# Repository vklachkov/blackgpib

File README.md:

# BlackGPIB

BlackGPIB is hardware that emulates GPIB disk drives for the GRiD Compass. It is based on the Raspberry Pi RP2040.

## Hardware

Hardware schematics and design files are located in the `hardware` folder. Production files are available in the [latest release](github.com/vklachkov/blackgpib/releases) on GitHub.

We recommend using the latest `pico` version. The list of components and known issues is described in the `README.md` file located in the `hardware/pico` directory.

## Firmware

The firmware source code is located in the `pico` folder.

The latest stable prebuilt firmware in UF2 format is available in the [latest release](https://github.com/vklachkov/blackgpib/releases) on GitHub.

### Flashing prebuilt firmware

To flash the firmware, hold the **BOOTSEL** button while connecting the Raspberry Pi Pico to your computer. The Pico will appear as a removable drive.

Copy the `blackgpib.uf2` file to this drive. The Pico will reboot automatically after the file is copied.

### Building firmware from source

To build the firmware yourself, install the Pico SDK first. Follow the instructions on the official Raspberry Pi website:

https://www.raspberrypi.com/documentation/microcontrollers/c_sdk.html

Then follow these steps.

1. Clone the repository:

```bash
git clone --depth 1 --recursive https://github.com/vklachkov/blackgpib
```

2. Go to the sources directory:

```bash
cd blackgpib/pico
```

3. Configure the project for your board:

```bash
cmake -S . -B build -DPICO_BOARD=pico
```

4. Build:

```bash
cmake --build build -j
```

5. Flash the firmware:

   Hold the **BOOTSEL** button while connecting the Raspberry Pi Pico to your computer. Then copy the `blackgpib.uf2` file from the `build` folder to the mounted Pico drive.

## How to use it?

After assembling and flashing the device, find a microSD card and format it as FAT32 or exFAT. Copy the disk images to this card. Insert the microSD card into BlackGPIB. Connect BlackGPIB to power, the LED should turn on after about one and a half seconds. After that, you can turn on the GRiD Compass. Enjoy!

### Which file formats are supported?

Currently, only .IMG files are supported. IMD and .CHD are not supported.

If you want to use IMD files from gridrepository.org, please use the [imd2raw](https://github.com/RetroFloppy/imd2raw) converter until BlackGPIB support is not available.

### How is the address selected?

For images that do not have a GPIB address specified in their filename, the address is selected automatically.

Floppy disk images use addresses 5, 6, and 13. Other images use the remaining default addresses (4, 5, 6, 12, 13).

If addresses conflict, or if there are no addresses left, an entry about this will be written to log.txt.

### How do I bind an image to a specific GPIB address?

Rename the image to FXX or HXX, where XX is the GPIB address. For example, FLOPPY4_TEST.IMG or HD12.IMG.

### How do I change the image geometry?

You can’t, it is selected automatically. Geometry configuration is not supported.

### Troubleshooting

**The LED is always off**

Check that you assembled the emulator correctly, powered it, and flashed the correct firmware.

**The device is steadily blinking the LED on the board**

This means that the device does not see the SD card, or the filesystem on it is not FAT.

Remove the SD card, format it again, and insert it into the device. If you did not disconnect power from BlackGPIB, then, if successful, the device will blink the LED several times, and then the LED should stay steadily on. This means that the device is ready to use.

**The device is blinking SOS**

This means that the device has gone into a boot loop. Normally, this should not happen.

Connect the device to your computer, open a serial port monitor, and check what went wrong before the boot loop. You can email me or open an issue, and I will try to help.

## License

This project is released under the [MIT License](LICENSE).

You are free to use, modify, and share it. I will be happy if BlackGPIB helps you bring your GRiD Compass back to life and use it again.

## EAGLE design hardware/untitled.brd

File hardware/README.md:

# First board by @JDat for Raspberry Pi 2+

This is the first revision of the board, designed by @JDat (also known as @YL3AKC):

> [!WARNING]
> It is better to wait for the second revision or new Pico base version. This board is still experimental.

## Components

| Part           | Value                | Package    | Quantity |
|----------------|----------------------|------------|----------|
| GPIB Connector | -                    | 90 Degree  | 1        |
| SN75160B       | -                    | SMD or DIP | 1        |
| SN75161B       | -                    | SMD or DIP | 1        |
| Resistor       | 2kΩ                  | 0805       | 20       |
| Capacitor      | 0.1uF                | 0805       | 2        |
| Pin Header     | 20x2 Straight Female | -          | 1        |

P.S. Instead of small SMD components, you can also use through-hole components, as Kirill @BOOtak Leyfer did.

https://t.me/bootaks_old_devices/286

## Errata

### ATN <-> SRQ

ATN and SRQ are mixed up on the board. Both the labels and the pins on the connector are swapped.

For the board to work correctly, you need to cut two tracks on the back side that go to SRQ and ATN, and solder two jumpers, as shown in the photo:

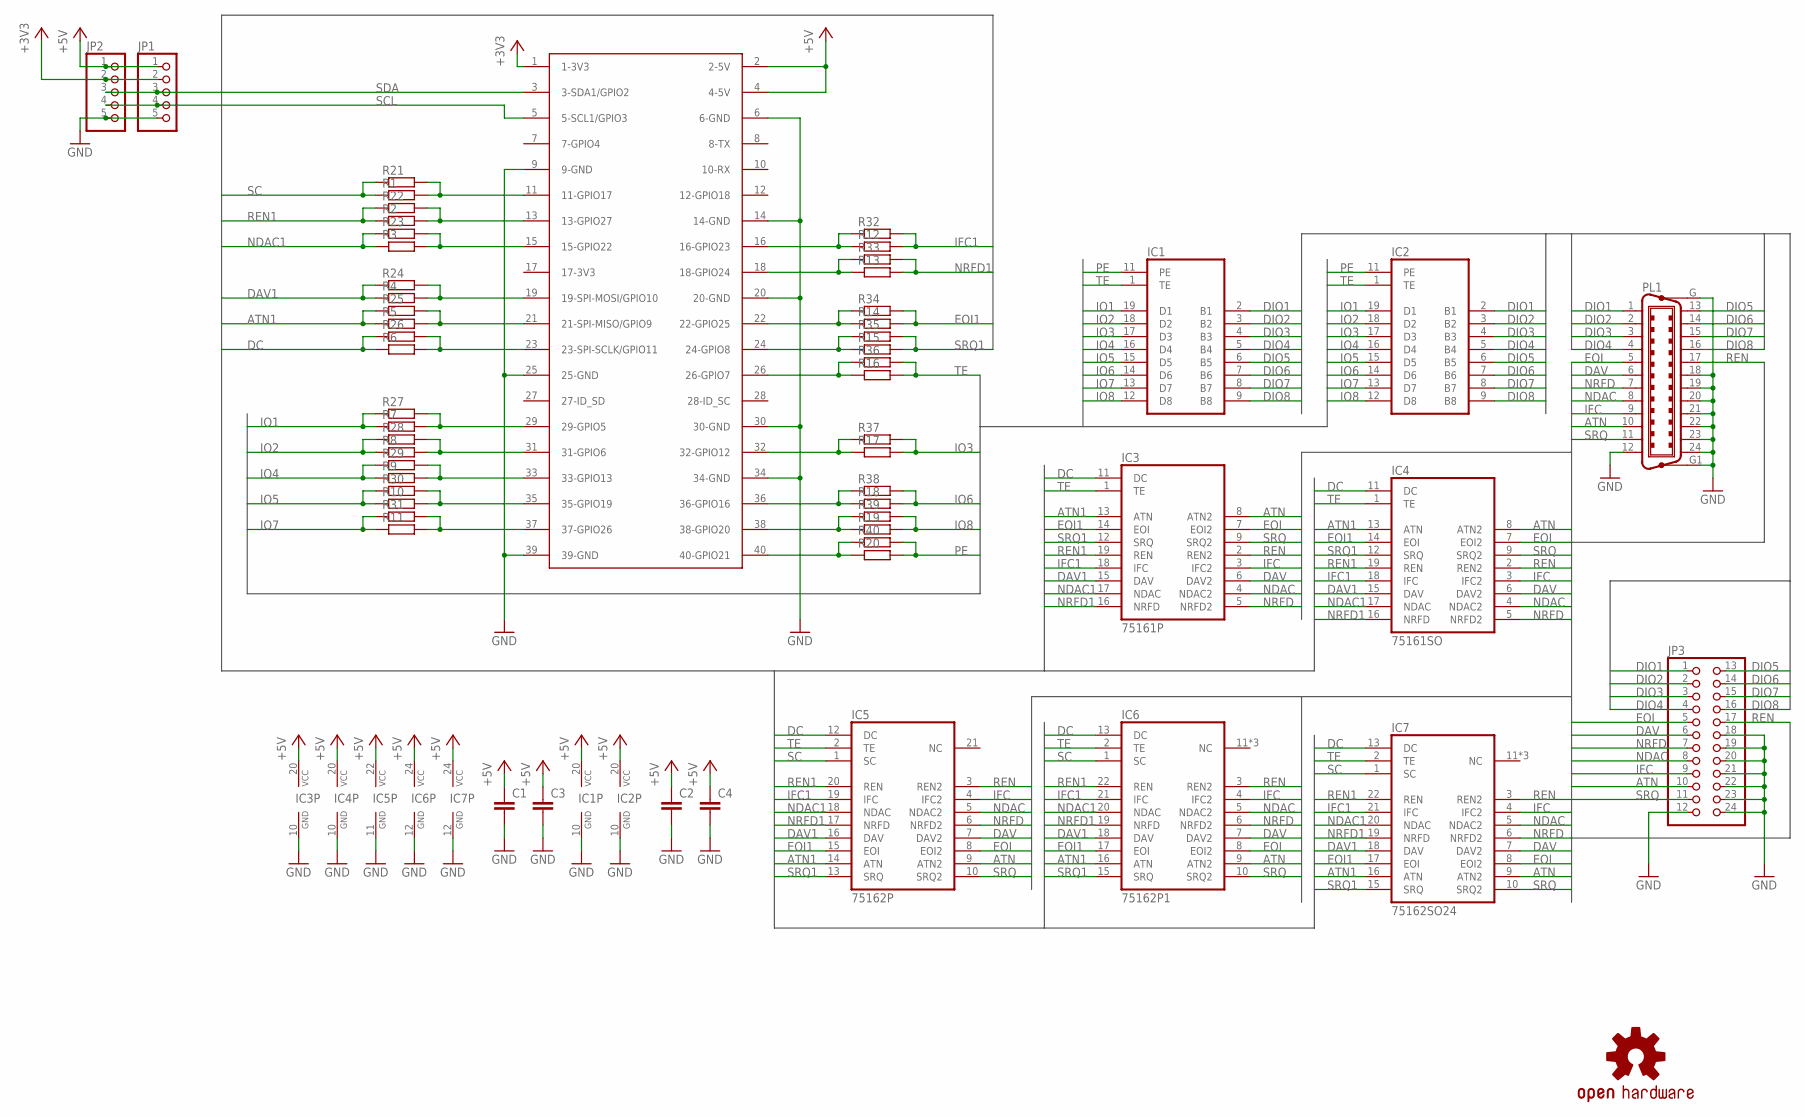
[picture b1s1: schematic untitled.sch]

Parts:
C1, C2: C-EUC0805; C0805
C3, C4: C-EU050-024X044; C050-024X044
IC1: 75160P; DIL20
IC2: 75160SO; SO20L
IC3: 75161P; DIL20
IC4: 75161SO; SO20L
IC5: 75162P; DIL22-3
IC6: 75162P1; DIL24-3
IC7: 75162SO24; SOIC127P1030X265-24N
JP1, JP2: PINHD-1X5; 1X05
JP3: GPIB-PINHD-2X12
LOGO2: OSHW-LOGOS; OSHW-LOGO-S
PL1: C24HP; 24HP
R1, R2, R3, R4, R5, R6, R7, R8, R9, R10, R11, R12, R13, R14, R15, R16, R17, R18, R19, R20: R-EU_R0805; R0805
R21, R22, R23, R24, R25, R26, R27, R28, R29, R30, R31, R32, R33, R34, R35, R36, R37, R38, R39, R40: R-EU_0204/7; 0204/7
U$2: RASPBERRY-PI+HEADERONLY; RASPBERRY-PI-PLUS-HEADERONLY

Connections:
+3V3: JP1.2, JP2.2, U$2.1 (1-3V3)
+5V: C1.1, C2.1, C3.1, C4.1, IC1.20 (VCC), IC2.20 (VCC), IC3.20 (VCC), IC4.20 (VCC), IC5.22 (VCC), IC6.24 (VCC), IC7.24 (VCC), JP1.1, JP2.1, U$2.2 (2-5V), U$2.4 (4-5V)
ATN: IC3.8 (ATN2), IC4.8 (ATN2), IC5.9 (ATN2), IC6.9 (ATN2), IC7.9 (ATN2), JP3.10, PL1.10
ATN1: IC3.13 (ATN), IC4.13 (ATN), IC5.14 (ATN), IC6.16 (ATN), IC7.16 (ATN), R5.1, R25.1
DAV: IC3.6 (DAV2), IC4.6 (DAV2), IC5.7 (DAV2), IC6.7 (DAV2), IC7.7 (DAV2), JP3.6, PL1.6
DAV1: IC3.15 (DAV), IC4.15 (DAV), IC5.16 (DAV), IC6.18 (DAV), IC7.18 (DAV), R4.1, R24.1
DC: IC3.11 (DC), IC4.11 (DC), IC5.12 (DC), IC6.13 (DC), IC7.13 (DC), R6.1, R26.1
DIO1: IC1.2 (B1), IC2.2 (B1), JP3.1, PL1.1
DIO2: IC1.3 (B2), IC2.3 (B2), JP3.2, PL1.2
DIO3: IC1.4 (B3), IC2.4 (B3), JP3.3, PL1.3
DIO4: IC1.5 (B4), IC2.5 (B4), JP3.4, PL1.4
DIO5: IC1.6 (B5), IC2.6 (B5), JP3.13, PL1.13
DIO6: IC1.7 (B6), IC2.7 (B6), JP3.14, PL1.14
DIO7: IC1.8 (B7), IC2.8 (B7), JP3.15, PL1.15
DIO8: IC1.9 (B8), IC2.9 (B8), JP3.16, PL1.16
EOI: IC3.7 (EOI2), IC4.7 (EOI2), IC5.8 (EOI2), IC6.8 (EOI2), IC7.8 (EOI2), JP3.5, PL1.5
EOI1: IC3.14 (EOI), IC4.14 (EOI), IC5.15 (EOI), IC6.17 (EOI), IC7.17 (EOI), R14.2, R34.2
GND: C1.2, C2.2, C3.2, C4.2, IC1.10 (GND), IC2.10 (GND), IC3.10 (GND), IC4.10 (GND), IC5.11 (GND), IC6.12 (GND), IC7.12 (GND), JP1.5, JP2.5, JP3.12, JP3.18, JP3.19, JP3.20, JP3.21, JP3.22, JP3.23, JP3.24, PL1.12, PL1.18, PL1.19, PL1.20, PL1.21, PL1.22, PL1.23, PL1.24, PL1.G, PL1.G1, U$2.6 (6-GND), U$2.9 (9-GND), U$2.14 (14-GND), U$2.20 (20-GND), U$2.25 (25-GND), U$2.30 (30-GND), U$2.34 (34-GND), U$2.39 (39-GND)
IFC: IC3.3 (IFC2), IC4.3 (IFC2), IC5.4 (IFC2), IC6.4 (IFC2), IC7.4 (IFC2), JP3.9, PL1.9
IFC1: IC3.18 (IFC), IC4.18 (IFC), IC5.19 (IFC), IC6.21 (IFC), IC7.21 (IFC), R12.2, R32.2
IO1: IC1.19 (D1), IC2.19 (D1), R7.1, R27.1
IO2: IC1.18 (D2), IC2.18 (D2), R8.1, R28.1
IO3: IC1.17 (D3), IC2.17 (D3), R17.2, R37.2
IO4: IC1.16 (D4), IC2.16 (D4), R9.1, R29.1
IO5: IC1.15 (D5), IC2.15 (D5), R10.1, R30.1
IO6: IC1.14 (D6), IC2.14 (D6), R18.2, R38.2
IO7: IC1.13 (D7), IC2.13 (D7), R11.1, R31.1
IO8: IC1.12 (D8), IC2.12 (D8), R19.2, R39.2
unnamed: R1.2, R21.2, U$2.11 (11-GPIO17)
unnamed: R2.2, R22.2, U$2.13 (13-GPIO27)
unnamed: R3.2, R23.2, U$2.15 (15-GPIO22)
unnamed: R4.2, R24.2, U$2.19 (19-SPI-MOSI/GPIO10)
unnamed: R5.2, R25.2, U$2.21 (21-SPI-MISO/GPIO9)
unnamed: R6.2, R26.2, U$2.23 (23-SPI-SCLK/GPIO11)
unnamed: R7.2, R27.2, U$2.29 (29-GPIO5)
unnamed: R8.2, R28.2, U$2.31 (31-GPIO6)
unnamed: R9.2, R29.2, U$2.33 (33-GPIO13)
unnamed: R10.2, R30.2, U$2.35 (35-GPIO19)
unnamed: R11.2, R31.2, U$2.37 (37-GPIO26)
unnamed: R12.1, R32.1, U$2.16 (16-GPIO23)
unnamed: R13.1, R33.1, U$2.18 (18-GPIO24)
unnamed: R14.1, R34.1, U$2.22 (22-GPIO25)
unnamed: R15.1, R35.1, U$2.24 (24-GPIO8)
unnamed: R16.1, R36.1, U$2.26 (26-GPIO7)
unnamed: R17.1, R37.1, U$2.32 (32-GPIO12)
unnamed: R18.1, R38.1, U$2.36 (36-GPIO16)
unnamed: R19.1, R39.1, U$2.38 (38-GPIO20)
unnamed: R20.1, R40.1, U$2.40 (40-GPIO21)
NDAC: IC3.4 (NDAC2), IC4.4 (NDAC2), IC5.5 (NDAC2), IC6.5 (NDAC2), IC7.5 (NDAC2), JP3.8, PL1.8
NDAC1: IC3.17 (NDAC), IC4.17 (NDAC), IC5.18 (NDAC), IC6.20 (NDAC), IC7.20 (NDAC), R3.1, R23.1
NRFD: IC3.5 (NRFD2), IC4.5 (NRFD2), IC5.6 (NRFD2), IC6.6 (NRFD2), IC7.6 (NRFD2), JP3.7, PL1.7
NRFD1: IC3.16 (NRFD), IC4.16 (NRFD), IC5.17 (NRFD), IC6.19 (NRFD), IC7.19 (NRFD), R13.2, R33.2
PE: IC1.11 (PE), IC2.11 (PE), R20.2, R40.2
REN: IC3.2 (REN2), IC4.2 (REN2), IC5.3 (REN2), IC6.3 (REN2), IC7.3 (REN2), JP3.17, PL1.17
REN1: IC3.19 (REN), IC4.19 (REN), IC5.20 (REN), IC6.22 (REN), IC7.22 (REN), R2.1, R22.1
SC: IC5.1 (SC), IC6.1 (SC), IC7.1 (SC), R1.1, R21.1
SCL: JP1.4, JP2.4, U$2.5 (5-SCL1/GPIO3)
SDA: JP1.3, JP2.3, U$2.3 (3-SDA1/GPIO2)
SRQ: IC3.9 (SRQ2), IC4.9 (SRQ2), IC5.10 (SRQ2), IC6.10 (SRQ2), IC7.10 (SRQ2), JP3.11, PL1.11
SRQ1: IC3.12 (SRQ), IC4.12 (SRQ), IC5.13 (SRQ), IC6.15 (SRQ), IC7.15 (SRQ), R15.2, R35.2
TE: IC1.1 (TE), IC2.1 (TE), IC3.1 (TE), IC4.1 (TE), IC5.2 (TE), IC6.2 (TE), IC7.2 (TE), R16.2, R36.2

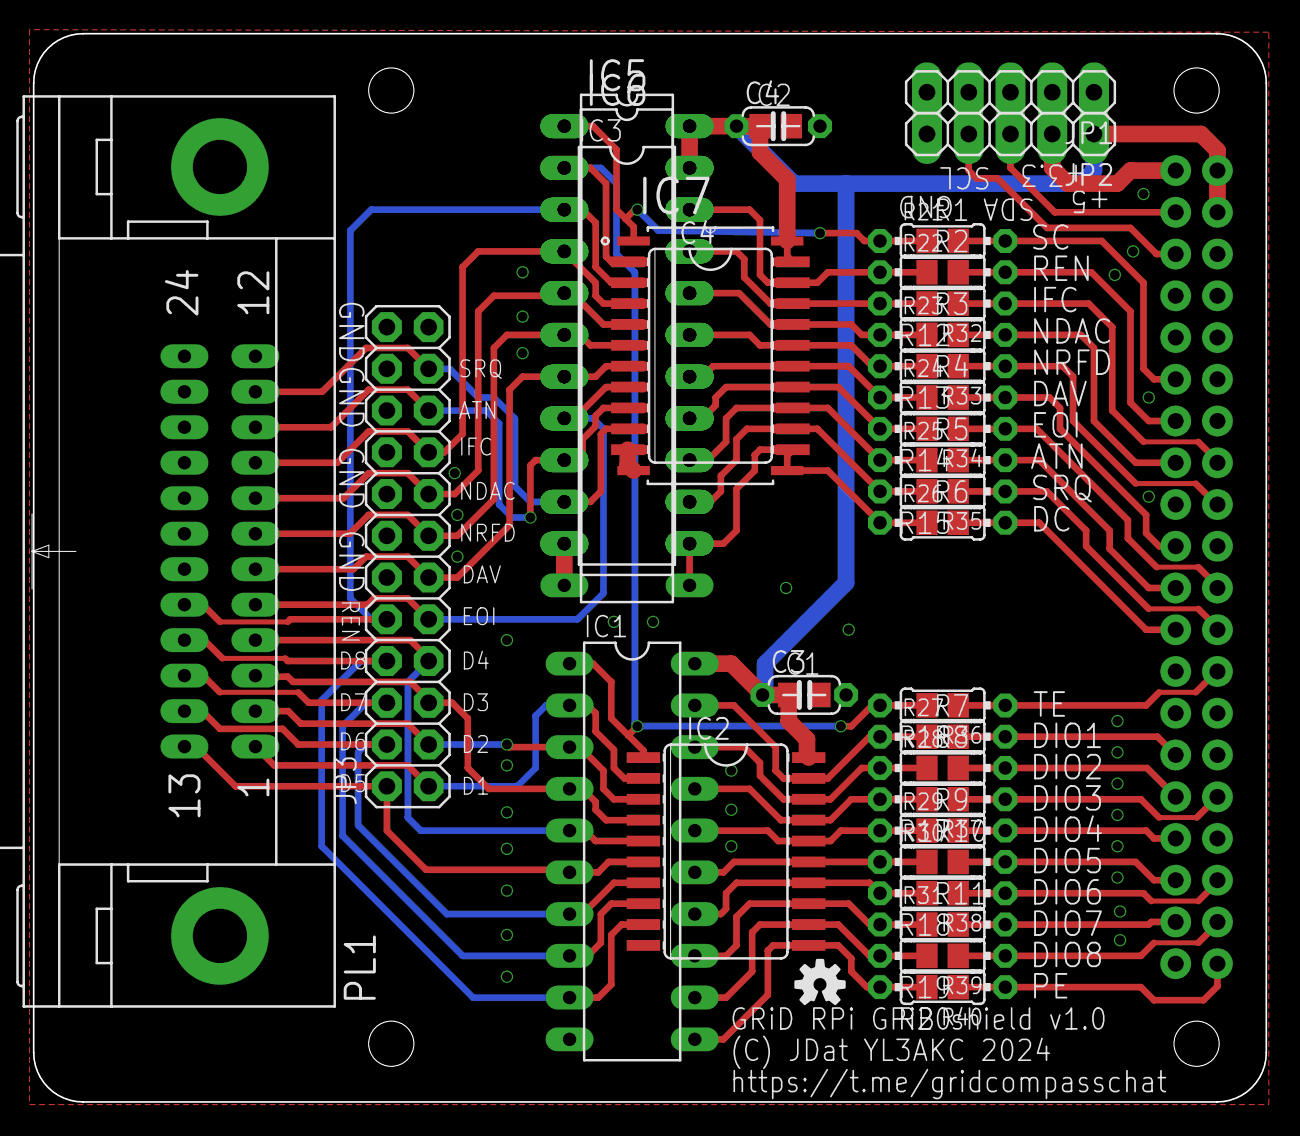
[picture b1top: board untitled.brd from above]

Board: 2 copper layers, 75.0 x 65.0 mm, 57 parts (0 on the bottom side), 61 nets.

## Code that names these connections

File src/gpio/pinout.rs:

//! Valid pin list for the BlackGPiB board.

#[derive(Clone, Copy, Debug)]
#[repr(u8)]
pub enum KnownPin {
    /// Transfer Enable/Talk Enable (SN75161 and 162).
    TE = 7,
    /// Direction Control (SN75161 and 162).
    DC = 11,
    /// System Control (SN75162 only).
    SC = 17,
    /// System Control (SN75161 and 162).
    PE = 21,

    /// Data Input/Output, bit 1.
    DIO1 = 5,
    /// Data Input/Output, bit 2.
    DIO2 = 6,
    /// Data Input/Output, bit 3.
    DIO3 = 12,
    /// Data Input/Output, bit 4.
    DIO4 = 13,
    /// Data Input/Output, bit 5.
    DIO5 = 19,
    /// Data Input/Output, bit 6.
    DIO6 = 16,
    /// Data Input/Output, bit 7.
    DIO7 = 26,
    /// Data Input/Output, bit 8.
    DIO8 = 20,

    /// Data Available.
    DAV = 10,
    /// Not Ready For Data.
    NRFD = 24,
    /// Not Data Accepted.
    NDAC = 22,

    /// Attention.
    ATN = 9,
    /// Interface Clear.
    IFC = 23,
    /// Service Request.
    SRQ = 8,
    /// Remote Enable.
    REN = 27,
    /// End Or Identify.
    EOI = 25,
}

impl KnownPin {
    pub const fn all() -> [Self; 20] {
        [
            KnownPin::TE,
            KnownPin::DC,
            KnownPin::SC,
            KnownPin::PE,
            KnownPin::DIO1,
            KnownPin::DIO2,
            KnownPin::DIO3,
            KnownPin::DIO4,
            KnownPin::DIO5,
            KnownPin::DIO6,
            KnownPin::DIO7,
            KnownPin::DIO8,
            KnownPin::DAV,
            KnownPin::NRFD,
            KnownPin::NDAC,
            KnownPin::ATN,
            KnownPin::IFC,
            KnownPin::SRQ,
            KnownPin::REN,
            KnownPin::EOI,
        ]
    }

    pub const fn data() -> [KnownPin; 8] {
        [
            KnownPin::DIO1,
            KnownPin::DIO2,
            KnownPin::DIO3,
            KnownPin::DIO4,
            KnownPin::DIO5,
            KnownPin::DIO6,
            KnownPin::DIO7,
            KnownPin::DIO8,
        ]
    }
}

const _: () = {
    let pins = KnownPin::all();

    let mut i = 0;
    while i < pins.len() {
        assert!((pins[i] as u8) < 32, "all pins must be in range 0..32");
        i += 1;
    }
};

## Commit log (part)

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2025-10-28 Kirill Leyfer's unfinished emulator
2025-10-29 add devcontainer to develop this project on Macbook
2025-10-29 try to adapt sources to the new board
2025-10-29 add rust to devcontainer for next version
2025-10-31 add docs for gpib controller and gpib standard
2025-10-31 newver: listen bytes on gpib bus
2025-10-31 newver: enable pullups in sn75161/162
2025-10-31 newver: fix byte read
2025-10-31 change project structure
2025-10-31 newver: move listener state machine to file, remove LADS state
2025-11-01 setup all data pins before read
2025-11-01 speedup data reading, fix last byte loss
    Compass reset data lines without waiting for the disk, without waiting for us to raise the NDAC. This is a violation of the standard, but there's nothing we can do about it. We just need to read the 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
    It's a dangerous situation, but there's no solution yet.
2025-11-01 unwrap all gpio errors, remove all ???????
2025-11-01 add first logs from new implementation
2025-11-01 add gpib pinout to docs
2025-11-01 newver: implement listener state machine
2025-11-01 move reader logic to Listener struct
2025-11-01 parse requests
2025-11-02 add more comments to Listener
2025-11-02 talker stub
2025-11-02 shitty talker
2025-11-03 describe all known and supported dev addresses as enum
2025-11-03 use log crate and hand made logger instead of println's
2025-11-03 add parser for gpib commands and remove all is_smth functions
2025-11-03 add ieee 488.2
2025-11-03 add more pain
2025-11-04 create disk info struct
    no more big, ugly and weird byte arrays
2025-11-04 remove unused commands from GPIBCommand, add tests
2025-11-04 add docs and basic tests for Request
2025-11-04 code refactoring and documentation
2025-11-04 add Makefile for build and deploy
2025-11-04 try to refactor listener
2025-11-05 move next command wait logic to main
2025-11-05 fix makefile
2025-11-06 first working version
2025-11-07 pass image as console argument
2025-11-07 try to docs DiskIdentity structure
2025-11-07 patch image in-memory on write request
2025-11-07 try to debug boot from emu
2025-11-07 first boot from emulator
2025-11-09 serialize GPIBCommand and write round trip tests
2025-11-09 add utils to Talker for future master variant
2025-11-09 break everything, prepare for rewriting
2025-11-09 remove thiserror dependency
2025-11-09 doc every field in DiskIdentity
2025-11-09 custom rt logger from Cursor
2025-11-10 revert "custom rt logger from Cursor"
    this reverts commit 42d3d88642f886ec6d2344506e6bbc0f9c20d821.
2025-11-10 write new very safe logger with ringbuf crate
2025-11-10 configure scheduler: set core affinity and process priority
2025-11-10 prototype of device manager
2025-11-10 implement disk emulator based on new api
2025-11-10 fix serial poll tracking, first boot with new disk emu
2025-11-11 implement in memory write for disk emulator
2025-11-11 refactor code, prepare for open source
2025-11-11 feeble attempt to tidy up repo
2025-11-11 experiments with plotter
2025-11-11 create common device that proxy listened data to unix socket
2025-11-12 broadcast to udp port instead of unix socket
2025-11-12 add experimental hack to wait next command after GPiB state breakage
2025-11-12 add JDat's board
2025-11-12 add first README
2025-11-12 configure log level
2025-11-12 remove images hardcode, use cli args
2025-11-12 add flag to enable trace or verbose logs
2025-11-12 clear buffer after request processing, fix crash on Write
2025-11-12 pass message by ref to logger
2025-11-12 temporary hack for issue #6, fix MS-DOS 2.11 boot
2025-11-12 hack Initialize request for issue #2, fix MS-DOS 2.00A boot
2025-12-01 pin blackgpib to core 3, without available parallelism math
2025-12-01 enable pullups, fix bus hang when second device connected
2025-12-01 mmap images, allow to write data to disk
2025-12-01 log byte on atn break
2025-12-06 implement Format request
2025-12-07 implement sniffer
    I'm too tired of the logic analyzer
2025-12-07 fix Format, initialize only first 8 bytes with 0xFF
2025-12-07 add response structure for disk emulator and fix response for Write req
2025-12-08 fix new dump parsing in gpib-dump-analyzer
2025-12-08 configure scheduller before running sniffer
2025-12-08 rework all logs in gpib-dump-analyzer
    display parsed and raw requests and responses, display serial poll bytes in full mode and refactor state handling
2025-12-08 rename analyzer to dump_parser
2025-12-08 parse disk status responses in gpib-dump-parser
2025-12-08 fix typo in DiskStatus
2025-12-09 rename folder devices to emulator
2025-12-09 change cli interface of dump analyzer
    use bpaf, return --compact instead of only_requests|full
2025-12-09 set SRQ after UNL, not after last byte
2025-12-09 connect only requested disks
    Previously, to debug the emulator with a real device on bus, it was necessary to comment some addresses in KnownDevices.
    Also emulator incorrectly handled "uninserted" image, which cause issues with laptop.
    There is no measurable difference in speed between the old approach and the new one, but this makes further improvements much easier.
2025-12-09 refactor new requests parser in disk emulator
2025-12-09 detect unformatted disks
2025-12-09 fix "Broken pipe" panic in gpib-dump-parser
2025-12-09 stub for controller emulator
2025-12-09 add some dumps from sniffer
2025-12-10 move emulator/manager to emulator/mod
2025-12-10 handle unsupported requests like real disk
2025-12-15 rewrite listener gpib handshake from scratch
    After reverse engineering the 2101 floppy drive firmware, it turned out
    that the floppy drive behaves differently on the bus.
    I decided not to follow the standard, but to transfer the logic from the
    original peripheral.
    This doesn’t fix anything explicitly, but now I’m confident in the
    correctness of the handshakes and command handling.
2025-12-16 slightly fix talker
2025-12-16 do not reset ndac if dav is high on command handshake
2025-12-16 fix serial poll state machine
2025-12-21 hack nanosleep with busy_wait
    fixes awful 2ms lag on gpio configuration
2025-12-21 wait atn inside talker
2025-12-22 fork rppal, remove all thread safe code and std::thread::sleep
2025-12-22 rewrite busy_wait using cntfrq и cntvct
2025-12-22 rename rppal to gpio, prepare for rewriting gpio part of project
2025-12-23 first step of gpio rewriting: break everything, reimplement listener
2025-12-23 reimplement talker using new gpio module
2025-12-23 implement read_dio in listener gpio
2025-12-23 configure all pins in listener and talker
2025-12-24 rework talker to dc=low, te=high and remove bias setup
2025-12-25 move system outside of gpio, open gpio in main
2025-12-25 remove all unused features from gpio, make it less unsafe
2025-12-25 move all gpib related code to gpib folder and reorganize utils
2025-12-25 rework error handling in main
2025-12-25 fix logs, add comments
2025-12-25 add doc comments for files from rppal
2025-12-26 disable priority configuration
2025-12-26 make talker logs less verbose
2025-12-26 configure gpio pins before touching SN7516x control pins
2025-12-26 restore sniffer
2025-12-26 fix structure of disk's StatusResponse
2025-12-26 rename drive_ready to drive_status and improve tests in disk emulator
2025-12-26 write diskette using blackgpib
2025-12-26 add OutOfBoundsWrite to DiskStatus
2025-12-26 add cli commands to read, write and format gpib disks
2025-12-26 implement reset and format in DeviceController
2025-12-26 fix code after bad rebase
2025-12-27 rework logs for controller mode, improve error handling
2025-12-27 fix talker and listener for controller mode (emulator still works)
2025-12-27 wait 15 seconds after reset like real laptop
2025-12-27 add "controller status" command to get info about gpib device
2025-12-28 move disk protocol files to crate level
2025-12-28 remove asserts in controller, replace with proper error handling
2025-12-28 rewrite logs and error in controller format command
2025-12-28 add more logs to controller mode
2025-12-28 prevent blackgpib from running on Raspberry Pi 1
    because blackgpib requires one dedicated core
2025-12-28 add delays to Talker::send_command
2025-12-28 remove all panics from emulator
2025-12-28 fix all TODOs in controller mode help
2025-12-29 Refactor disk protocol
2025-12-29 check mode instead of sector when handling Write(0xFFFFFFFF) request
2026-01-13 update disk protocol after reverse engineering 2101
2026-02-01 add pico hatted board schematic
2026-02-01 add pico hello world
2026-02-01 fix pico hatted version: swap dc te and fix dc te on schematic
2026-02-02 move board from @JDat to separate folder
2026-02-02 move linux version source code to subdirectory "pi"
2026-02-03 pi pico demo firmware (just to test hardware)
2026-02-07 fix voltage divider for pico hat hardware
2026-02-07 fix gpib address in pico firmware
2026-02-07 continue debugging pico version
2026-02-08 pico: fix handshakes in listening function
2026-02-08 pico: fix logs, continue debugging
2026-02-08 pico: invert bits when sending byte
2026-02-08 pico: fix request handling
2026-02-08 pico: split request handling to multiple functions
2026-02-08 pico: fix srq handling, first boot without any timeout issues
2026-02-08 pico: read/write data from/to sd card
2026-02-09 pico: split firmware into multiple files
2026-02-10 optimize gpib pins configuration
2026-02-11 pico: optimize hatted version for SLA printer, remove optional components
2026-02-14 pico: add ground polygon and improve traces in hatted version
2026-02-15 pico: move DC TE traces in hatted version to make handicraft easier
2026-02-15 pico: fix several warnings and UBs
2026-02-18 pi: swap srq and atn on the gpib hat and fix import issues
2026-02-19 pi: update README.md for hardware
2026-02-23 pico: add rev 1 board
2026-02-23 pico: add 47uF tantalum capacitor near sd card slot to rev 1 board
2026-02-23 pico: fix disconnected pads and zones on rev 1 board
2026-05-09 pico: fix pinout for rev 1 board, configure PE
2026-06-01 rewrite readme for all folders, add license and remove old pdf files
2026-06-01 fix main readme license section header
2026-06-01 pico: move all file operations to loaders, handle sd card errors
2026-06-01 pico: blink on gpib activity
2026-06-01 pico: replace all printfs with LOG_* macro, disable debug logs
2026-06-01 pico: support multiple devices, but still use demo images
2026-06-02 pico: guess geometry in img loader
2026-06-02 pico: select disk parameters based on image geometry
2026-06-02 pico: support image formatting
2026-06-02 pico: code format, fix compilation
2026-06-02 pico: fix handshake for MLA gpib command
2026-06-04 pico: load list of images from sd card, move sd card ops to sd_card.c
2026-06-04 pico: refactor logging, save some logs to sd card
2026-06-04 pico: reboot loop protection to save sd card
2026-06-04 pico: do not remount fs in sd_card_get_image_loaders, fix boot
2026-06-04 pico: add more logs for errors
2026-06-04 pico: sync files after write
2026-06-04 pico: add manual to README.md

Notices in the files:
parts and their libraries:
SparkFun-Aesthetics: Licensing: Creative Commons ShareAlike 4.0 International - https://creativecommons.org/licenses/by-sa/4.0
